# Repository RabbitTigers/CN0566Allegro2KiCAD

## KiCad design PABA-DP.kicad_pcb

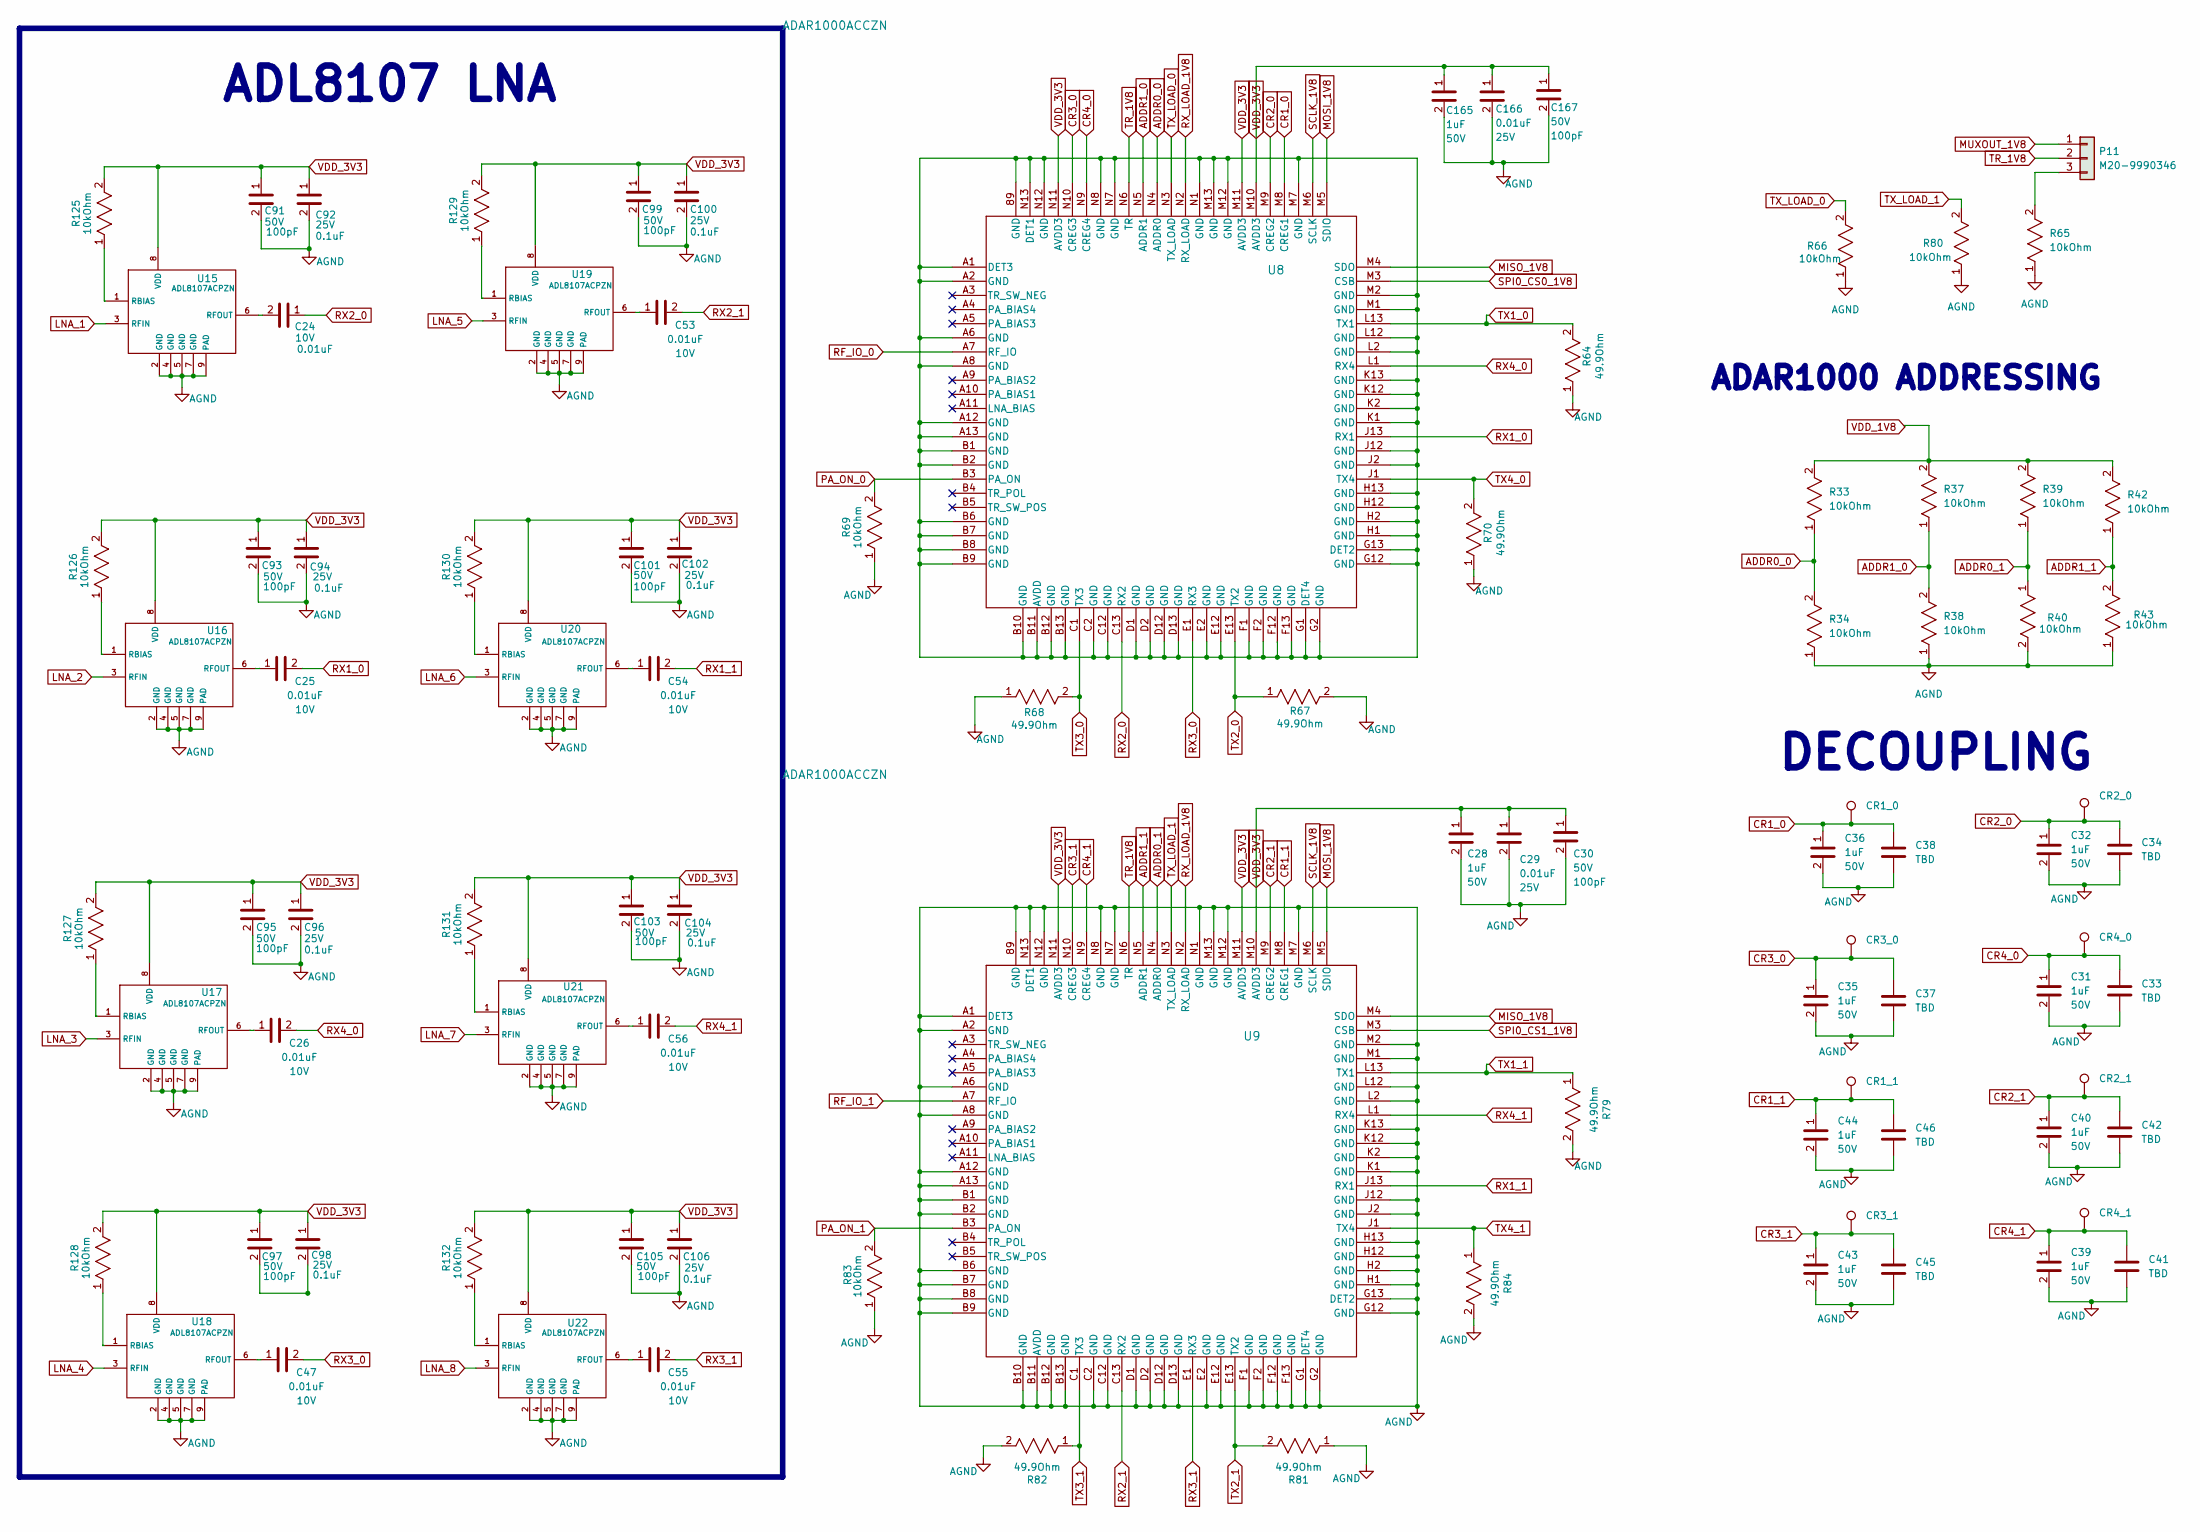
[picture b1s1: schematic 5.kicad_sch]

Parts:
C24, C25, C26, C47, C53, C54, C55, C56: GRM033R71A103KA01D; C_0201_0603Metric
C28, C31, C32, C35, C36, C39, C40, C43, C44, C165: CL10A105KB8NNNC; C_0603_1608Metric
C29, C166: CL10B103KA8NNNC; C_0603_1608Metric
C30, C91, C93, C95, C97, C99, C101, C103, C105, C167: CC0603KRX7R9BB101; C_0603_1608Metric
C33, C34, C37, C38, C41, C42, C45, C46: TBD; C_0402_1005Metric
C92, C94, C96, C98, C100, C102, C104, C106: CL10B104KA8NNNC; C_0603_1608Metric
CR1_0, CR1_1, CR2_0, CR2_1, CR3_0, CR3_1, CR4_0, CR4_1: TestPoint; Testpoint
P11: M20-9990346; PinHeader_1x03_P2.54mm_Vertical
R33, R34, R37, R38, R39, R40, R42, R43, R65, R66, R69, R80, R83, R125, R126, R127, R128, R129, R130, R131, R132: ERJ-3EKF1002V; R_0603_1608Metric
R64, R67, R68, R70, R79, R81, R82, R84: ERJ-1GNF49R9C; R_0201_0603Metric
U8, U9: ADAR1000ACCZN
U15, U16, U17, U18, U19, U20, U21, U22: ADL8107ACPZN; ADL8107ACPZN-R7

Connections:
ADDR0_0: U8.N4 (ADDR0)
ADDR0_1: R39.1, R40.1, U9.N4 (ADDR0)
ADDR1_0: R37.1, R38.2, U8.N5 (ADDR1)
ADDR1_1: R42.1, R43.2, U9.N5 (ADDR1)
AGND: C28.2, C29.2, C30.2, C31.2, C32.2, C33.2, C34.2, C35.2, C36.2, C37.2, C38.2, C39.2, C40.2, C41.2, C42.2, C43.2, C44.2, C45.2, C46.2, C91.2, C92.2, C93.2, C94.2, C95.2, C96.2, C99.2, C100.2, C101.2, C102.2, C103.2, C104.2, C105.2, C106.2, C165.2, C166.2, C167.2, R34.1, R38.1, R40.2, R43.1, R64.1, R65.1, R66.1, R67.2, R68.1, R69.1, R70.1, R79.2, R80.1, R81.1, R82.2, R83.1, R84.2, U9.89 (GND), U9.A1 (DET3), U9.A2 (GND), U9.A6 (GND), U9.A8 (GND), U9.A12 (GND), U9.A13 (GND), U9.B1 (GND), U9.B2 (GND), U9.B6 (GND), U9.B7 (GND), U9.B8 (GND), U9.B9 (GND), U9.B10 (GND), U9.B11 (AVDD), U9.B12 (GND), U9.B13 (GND), U9.C2 (GND), U9.C12 (GND), U9.D1 (GND), U9.D2 (GND), U9.D12 (GND), U9.D13 (GND), U9.E2 (GND), U9.E12 (GND), U9.F1 (GND), U9.F2 (GND), U9.F12 (GND), U9.F13 (GND), U9.G1 (DET4), U9.G2 (GND), U9.G12 (GND), U9.G13 (DET2), U9.H1 (GND), U9.H2 (GND), U9.H12 (GND), U9.H13 (GND), U9.J2 (GND), U9.J12 (GND), U9.K1 (GND), U9.K2 (GND), U9.K12 (GND), U9.K13 (GND), U9.L2 (GND), U9.L12 (GND), U9.M1 (GND), U9.M2 (GND), U9.M7 (GND), U9.M12 (GND), U9.M13 (GND), U9.N1 (GND), U9.N7 (GND), U9.N8 (GND), U9.N12 (GND), U9.N13 (DET1), U15.2 (GND), U15.4 (GND), U15.5 (GND), U15.7 (GND), U15.9 (PAD), U16.2 (GND), U16.4 (GND), U16.5 (GND), U16.7 (GND), U16.9 (PAD), U17.2 (GND), U17.4 (GND), U17.5 (GND), U17.7 (GND), U17.9 (PAD), U18.2 (GND), U18.4 (GND), U18.5 (GND), U18.7 (GND), U18.9 (PAD), U19.2 (GND), U19.4 (GND), U19.5 (GND), U19.7 (GND), U19.9 (PAD), U20.2 (GND), U20.4 (GND), U20.5 (GND), U20.7 (GND), U20.9 (PAD), U21.2 (GND), U21.4 (GND), U21.5 (GND), U21.7 (GND), U21.9 (PAD), U22.2 (GND), U22.4 (GND), U22.5 (GND), U22.7 (GND), U22.9 (PAD); also elsewhere on the board
CR1_0: C36.1, C38.1, CR1_0.1, U8.M8 (CREG1)
CR1_1: C44.1, C46.1, CR1_1.1, U9.M8 (CREG1)
CR2_0: C32.1, C34.1, CR2_0.1, U8.M9 (CREG2)
CR2_1: C40.1, C42.1, CR2_1.1, U9.M9 (CREG2)
CR3_0: C35.1, C37.1, CR3_0.1, U8.N10 (CREG3)
CR3_1: C43.1, C45.1, CR3_1.1, U9.N10 (CREG3)
CR4_0: C31.1, C33.1, CR4_0.1, U8.N9 (CREG4)
CR4_1: C39.1, C41.1, CR4_1.1, U9.N9 (CREG4)
LNA_1: U15.3 (RFIN); also elsewhere on the board
LNA_2: U16.3 (RFIN); also elsewhere on the board
LNA_3: U17.3 (RFIN); also elsewhere on the board
LNA_4: U18.3 (RFIN); also elsewhere on the board
LNA_5: U19.3 (RFIN); also elsewhere on the board
LNA_6: U20.3 (RFIN); also elsewhere on the board
LNA_7: U21.3 (RFIN); also elsewhere on the board
LNA_8: U22.3 (RFIN); also elsewhere on the board
MISO_1V8: U8.M4 (SDO), U9.M4 (SDO); also elsewhere on the board
MOSI_1V8: U8.M5 (SDIO), U9.M5 (SDIO); also elsewhere on the board
MUXOUT_1V8: P11.1; also elsewhere on the board
unnamed: C97.2, C98.2
unnamed: P11.3, R65.2
unnamed: R33.1, R34.2
unnamed: U8.89 (GND), U8.A1 (DET3), U8.A2 (GND), U8.A6 (GND), U8.A8 (GND), U8.A12 (GND), U8.A13 (GND), U8.B1 (GND), U8.B2 (GND), U8.B6 (GND), U8.B7 (GND), U8.B8 (GND), U8.B9 (GND), U8.B10 (GND), U8.B11 (AVDD), U8.B12 (GND), U8.B13 (GND), U8.C2 (GND), U8.C12 (GND), U8.D1 (GND), U8.D2 (GND), U8.D12 (GND), U8.D13 (GND), U8.E2 (GND), U8.E12 (GND), U8.F1 (GND), U8.F2 (GND), U8.F12 (GND), U8.F13 (GND), U8.G1 (DET4), U8.G2 (GND), U8.G12 (GND), U8.G13 (DET2), U8.H1 (GND), U8.H2 (GND), U8.H12 (GND), U8.H13 (GND), U8.J2 (GND), U8.J12 (GND), U8.K1 (GND), U8.K2 (GND), U8.K12 (GND), U8.K13 (GND), U8.L2 (GND), U8.L12 (GND), U8.M1 (GND), U8.M2 (GND), U8.M7 (GND), U8.M12 (GND), U8.M13 (GND), U8.N1 (GND), U8.N7 (GND), U8.N8 (GND), U8.N12 (GND), U8.N13 (DET1)
unnamed: R125.1, U15.1 (RBIAS)
unnamed: C24.2, U15.6 (RFOUT)
unnamed: R126.1, U16.1 (RBIAS)
unnamed: C25.1, U16.6 (RFOUT)
unnamed: R127.1, U17.1 (RBIAS)
unnamed: C26.1, U17.6 (RFOUT)
unnamed: R128.1, U18.1 (RBIAS)
unnamed: C47.1, U18.6 (RFOUT)
unnamed: R129.1, U19.1 (RBIAS)
unnamed: C53.1, U19.6 (RFOUT)
unnamed: R130.1, U20.1 (RBIAS)
unnamed: C54.1, U20.6 (RFOUT)
unnamed: R131.1, U21.1 (RBIAS)
unnamed: C56.1, U21.6 (RFOUT)
unnamed: R132.1, U22.1 (RBIAS)
unnamed: C55.1, U22.6 (RFOUT)
PA_ON_0: R69.2, U8.B3 (PA_ON)
PA_ON_1: R83.2, U9.B3 (PA_ON)
RF_IO_0: U8.A7 (RF_IO); also elsewhere on the board
RF_IO_1: U9.A7 (RF_IO); also elsewhere on the board
RX1_0: C25.2, U8.J13 (RX1)
RX1_1: C54.2, U9.J13 (RX1)
RX2_0: C24.1, U8.C13 (RX2)
RX2_1: C53.2, U9.C13 (RX2)
RX3_0: C47.2, U8.E1 (RX3)
RX3_1: C55.2, U9.E1 (RX3)
RX4_0: C26.2, U8.L1 (RX4)
RX4_1: C56.2, U9.L1 (RX4)
RX_LOAD_1V8: U8.N2 (RX_LOAD), U9.N2 (RX_LOAD); also elsewhere on the board
SCLK_1V8: U8.M6 (SCLK), U9.M6 (SCLK); also elsewhere on the board
SPI0_CS0_1V8: U8.M3 (CSB); also elsewhere on the board
SPI0_CS1_1V8: U9.M3 (CSB); also elsewhere on the board
TR_1V8: P11.2, U8.N6 (TR), U9.N6 (TR); also elsewhere on the board
TX1_0: R64.2, U8.L13 (TX1)
TX1_1: R79.1, U9.L13 (TX1)
TX2_0: R67.1, U8.E13 (TX2)
TX2_1: R81.2, U9.E13 (TX2)
TX3_0: R68.2, U8.C1 (TX3)
TX3_1: R82.1, U9.C1 (TX3)
TX4_0: R70.2, U8.J1 (TX4)
TX4_1: R84.1, U9.J1 (TX4)
TX_LOAD_0: R66.2, U8.N3 (TX_LOAD)
TX_LOAD_1: R80.2, U9.N3 (TX_LOAD)
VDD_1V8: R33.2, R37.2, R39.2, R42.2; also elsewhere on the board
VDD_3V3: C28.1, C29.1, C30.1, C91.1, C92.1, C93.1, C94.1, C95.1, C96.1, C97.1, C98.1, C99.1, C100.1, C101.1, C102.1, C103.1, C104.1, C105.1, C106.1, C165.1, C166.1, C167.1, R125.2, R126.2, R127.2, R128.2, R129.2, R130.2, R131.2, R132.2, U8.M10 (AVDD3), U8.M11 (AVDD3), U8.N11 (AVDD3), U9.M10 (AVDD3), U9.M11 (AVDD3), U9.N11 (AVDD3), U15.8 (VDD), U16.8 (VDD), U17.8 (VDD), U18.8 (VDD), U19.8 (VDD), U20.8 (VDD), U21.8 (VDD), U22.8 (VDD); also elsewhere on the board

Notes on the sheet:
ADL8107 LNA
ADAR1000 ADDRESSING
DECOUPLING

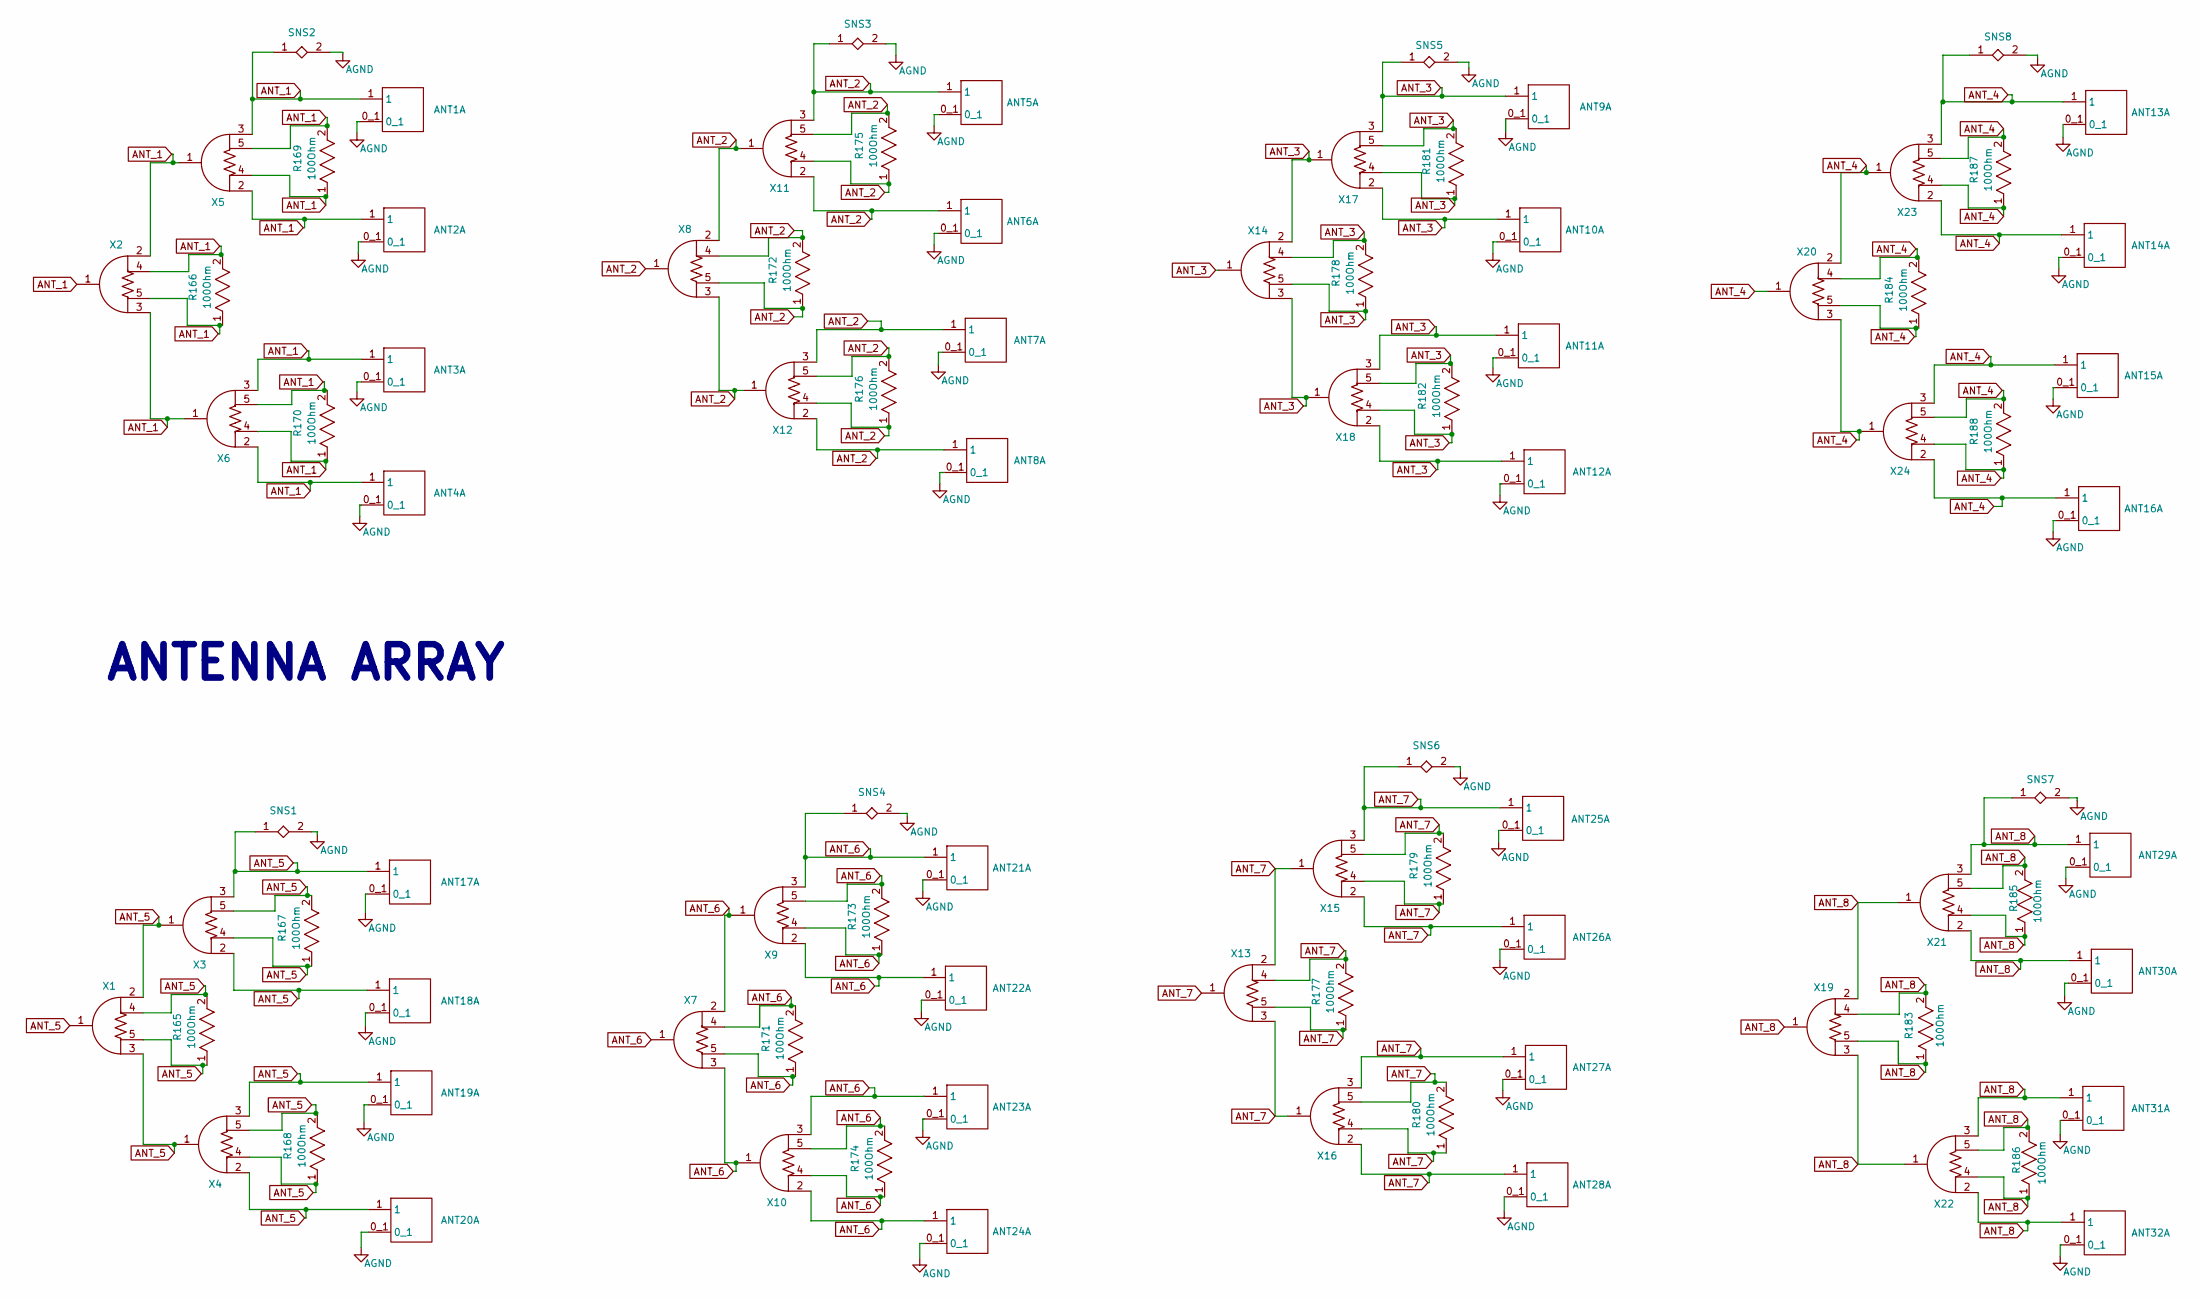
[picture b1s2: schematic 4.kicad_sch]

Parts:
ANT1, ANT2, ANT3, ANT4, ANT5, ANT6, ANT7, ANT8, ANT9, ANT10, ANT11, ANT12, ANT13, ANT14, ANT15, ANT16, ANT17, ANT18, ANT19, ANT20, ANT21, ANT22, ANT23, ANT24, ANT25, ANT26, ANT27, ANT28, ANT29, ANT30, ANT31, ANT32: Patch_Ant; Patch Antenna
R165, R166, R167, R168, R169, R170, R171, R172, R173, R174, R175, R176, R177, R178, R179, R180, R181, R182, R183, R184, R185, R186, R187, R188: ERJ-2RKF1000X; R_0402_1005Metric
SNS1, SNS2, SNS3, SNS4, SNS5, SNS6, SNS7, SNS8: NCSNS20MILL; SNS50Mill
X1, X2, X3, X4, X5, X6, X7, X8, X9, X10, X11, X12, X13, X14, X15, X16, X17, X18, X19, X20, X21, X22, X23, X24: 5P_Wilkinson_Divider; 5Pos Wilkinson divider

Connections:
AGND: ANT1.0_1, ANT2.0_1, ANT3.0_1, ANT4.0_1, ANT5.0_1, ANT6.0_1, ANT7.0_1, ANT8.0_1, ANT9.0_1, ANT10.0_1, ANT11.0_1, ANT12.0_1, ANT13.0_1, ANT14.0_1, ANT15.0_1, ANT16.0_1, ANT17.0_1, ANT18.0_1, ANT19.0_1, ANT20.0_1, ANT21.0_1, ANT22.0_1, ANT23.0_1, ANT24.0_1, ANT25.0_1, ANT26.0_1, ANT27.0_1, ANT28.0_1, ANT29.0_1, ANT30.0_1, ANT31.0_1, ANT32.0_1, SNS1.2, SNS2.2, SNS3.2, SNS4.2, SNS5.2, SNS6.2, SNS7.2, SNS8.2; also elsewhere on the board
ANT_1: ANT1.1, ANT2.1, ANT3.1, ANT4.1, R166.1, R166.2, R169.1, R169.2, R170.1, R170.2, SNS2.1, X2.1, X2.2, X2.3, X2.4, X2.5, X5.1, X5.2, X5.3, X5.4, X5.5, X6.1, X6.2, X6.3, X6.4, X6.5; also elsewhere on the board
ANT_2: ANT5.1, ANT6.1, ANT7.1, ANT8.1, R172.1, R172.2, R175.1, R175.2, R176.1, R176.2, SNS3.1, X8.1, X8.2, X8.3, X8.4, X8.5, X11.1, X11.2, X11.3, X11.4, X11.5, X12.1, X12.2, X12.3, X12.4, X12.5; also elsewhere on the board
ANT_3: ANT9.1, ANT10.1, ANT11.1, ANT12.1, R178.1, R178.2, R181.1, R181.2, R182.1, R182.2, SNS5.1, X14.1, X14.2, X14.3, X14.4, X14.5, X17.1, X17.2, X17.3, X17.4, X17.5, X18.1, X18.2, X18.3, X18.4, X18.5; also elsewhere on the board
ANT_4: ANT13.1, ANT14.1, ANT15.1, ANT16.1, R184.1, R184.2, R187.1, R187.2, R188.1, R188.2, SNS8.1, X20.1, X20.2, X20.3, X20.4, X20.5, X23.1, X23.2, X23.3, X23.4, X23.5, X24.1, X24.2, X24.3, X24.4, X24.5; also elsewhere on the board
ANT_5: ANT17.1, ANT18.1, ANT19.1, ANT20.1, R165.1, R165.2, R167.1, R167.2, R168.1, R168.2, SNS1.1, X1.1, X1.2, X1.3, X1.4, X1.5, X3.1, X3.2, X3.3, X3.4, X3.5, X4.1, X4.2, X4.3, X4.4, X4.5; also elsewhere on the board
ANT_6: ANT21.1, ANT22.1, ANT23.1, ANT24.1, R171.1, R171.2, R173.1, R173.2, R174.1, R174.2, SNS4.1, X7.1, X7.2, X7.3, X7.4, X7.5, X9.1, X9.2, X9.3, X9.4, X9.5, X10.1, X10.2, X10.3, X10.4, X10.5; also elsewhere on the board
ANT_7: ANT25.1, ANT26.1, ANT27.1, ANT28.1, R177.1, R177.2, R179.1, R179.2, R180.1, R180.2, SNS6.1, X13.1, X13.2, X13.3, X13.4, X13.5, X15.1, X15.2, X15.3, X15.4, X15.5, X16.1, X16.2, X16.3, X16.4, X16.5; also elsewhere on the board
ANT_8: ANT29.1, ANT30.1, ANT31.1, ANT32.1, R183.1, R183.2, R185.1, R185.2, R186.1, R186.2, SNS7.1, X19.1, X19.2, X19.3, X19.4, X19.5, X21.1, X21.2, X21.3, X21.4, X21.5, X22.1, X22.2, X22.3, X22.4, X22.5; also elsewhere on the board

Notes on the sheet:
ANTENNA ARRAY

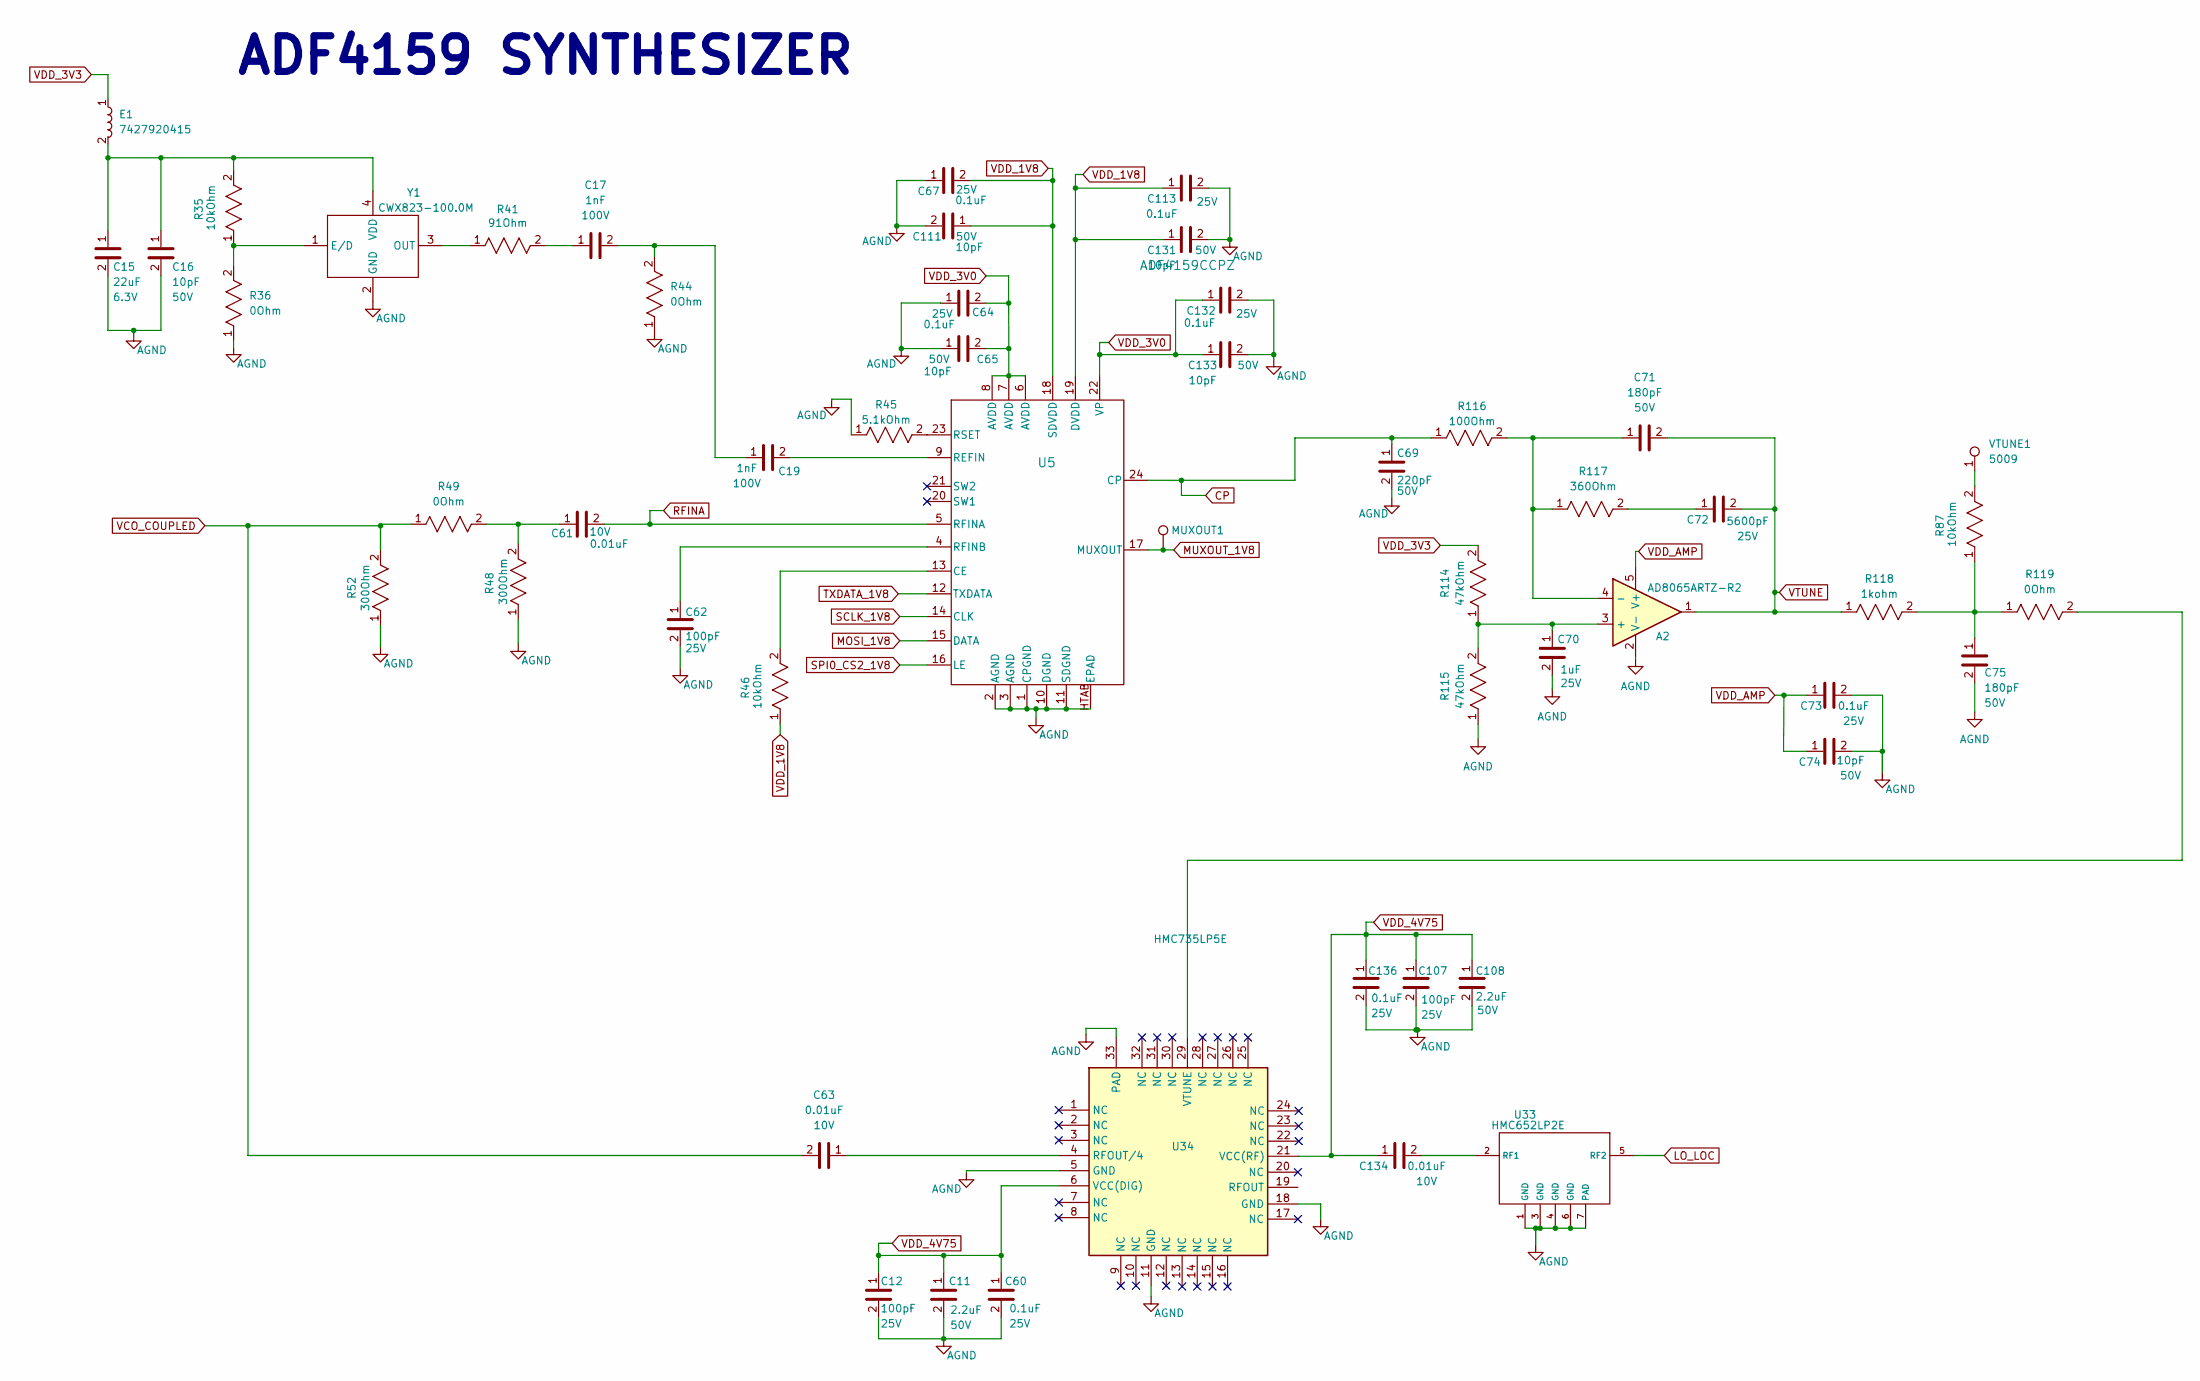
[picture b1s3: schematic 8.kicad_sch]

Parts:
A2: AD8065ARTZ-R2; SOT-23-5
C11, C108: GRM188R61H225KE11J; C_0603_1608Metric
C12, C62, C107: GRM033R71E101KA01D; C_0201_0603Metric
C15: GRM21BR60J226ME39L; C_0805_2012Metric
C16, C65, C74, C111, C131, C133: CC0402JRNPO9BN100; C_0402_1005Metric
C17, C19: 06031C102KAT2A; C_0603_1608Metric
C60, C64, C67, C73, C113, C132, C136: GRM155R71E104KE14D; C_0402_1005Metric
C61, C63, C134: GRM033R71A103KA01D; C_0201_0603Metric
C69: GRM0335C1H221JA01D; C_0201_0603Metric
C70: C1005X5R1E105K050BC; C_0402_1005Metric
C71, C75: CL05C181JB5NNNC; C_0402_1005Metric
C72: C0603C562J3GACTU; C_0603_1608Metric
E1: 7427920415; L_0805_2012Metric_Pad1.05x1.20mm_HandSolder
MUXOUT1: TestPoint; Testpoint
R35, R46, R87: ERJ-1GNF1002C; R_0201_0603Metric
R36, R44, R49, R119: ERJ-2GE0R00X; R_0402_1005Metric
R41: RC0603FR-0791RL; R_0603_1608Metric
R45: ERJ-1GNF5101C; R_0201_0603Metric
R48, R52: ERJ-1GNF3000C; R_0201_0603Metric
R114, R115: ERJ-1GNF4702C; R_0201_0603Metric
R116: ERJ-2RKF1000X; R_0402_1005Metric
R117: ERJ-2GEJ361X; R_0402_1005Metric
R118: ERJ-1GNF1001C; R_0201_0603Metric
U5: ADF4159CCPZ
U33: HMC652LP2E; HMC652LP2E TDFN 2x2
U34: HMC735LP5E; QFN-32-1EP_5x5mm_P0.5mm_EP3.7x3.7mm
VTUNE1: 5009; KEYSTONE_5009
Y1: CWX823-100.0M

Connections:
AGND: A2.2 (V-), C11.2, C12.2, C15.2, C16.2, C60.2, C62.2, C64.1, C65.1, C67.1, C69.2, C70.2, C73.2, C74.2, C75.2, C107.2, C108.2, C111.2, C113.2, C131.2, C132.2, C133.2, C136.2, R36.1, R44.1, R45.1, R48.1, R52.1, R115.1, U5.1 (CPGND), U5.2 (AGND), U5.3 (AGND), U5.10 (DGND), U5.11 (SDGND), U5.HTAB (EPAD), U33.1 (GND), U33.3 (GND), U33.4 (GND), U33.6 (GND), U33.7 (PAD), U34.5 (GND), U34.11 (GND), U34.18 (GND), U34.33 (PAD), Y1.2 (GND); also elsewhere on the board
CP: C69.1, R116.1, U5.24 (CP)
LO_LOC: U33.5 (RF2); also elsewhere on the board
MOSI_1V8: U5.15 (DATA); also elsewhere on the board
MUXOUT_1V8: MUXOUT1.1, U5.17 (MUXOUT); also elsewhere on the board
unnamed: A2.3 (+), C70.1, R114.1, R115.2
unnamed: A2.4 (-), C71.1, R116.2, R117.1
unnamed: C17.1, R41.2
unnamed: C17.2, C19.1, R44.2
unnamed: C61.1, R48.2, R49.2
unnamed: C72.1, R117.2
unnamed: C75.1, R87.1, R118.2, R119.1
unnamed: R87.2, VTUNE1.1
unnamed: R46.2, U5.13 (CE)
unnamed: C19.2, U5.9 (REFIN)
unnamed: C62.1, U5.4 (RFINB)
unnamed: R45.2, U5.23 (RSET)
unnamed: C134.2, U33.2 (RF1)
unnamed: C63.1, U34.4 (RFOUT/4)
unnamed: R119.2, U34.29 (VTUNE)
unnamed: R35.1, R36.2, Y1.1 (E/D)
unnamed: R41.1, Y1.3 (OUT)
unnamed: C15.1, C16.1, E1.2, R35.2, Y1.4 (VDD)
RFINA: C61.2, U5.5 (RFINA)
SCLK_1V8: U5.14 (CLK); also elsewhere on the board
SPI0_CS2_1V8: U5.16 (LE); also elsewhere on the board
TXDATA_1V8: U5.12 (TXDATA); also elsewhere on the board
VCO_COUPLED: C63.2, R49.1, R52.2
VDD_1V8: C67.2, C111.1, C113.1, C131.1, R46.1, U5.18 (SDVDD), U5.19 (DVDD); also elsewhere on the board
VDD_3V0: C64.2, C65.2, C132.1, C133.1, U5.6 (AVDD), U5.7 (AVDD), U5.8 (AVDD), U5.22 (VP); also elsewhere on the board
VDD_3V3: E1.1, R114.2; also elsewhere on the board
VDD_4V75: C11.1, C12.1, C60.1, C107.1, C108.1, C134.1, C136.1, U34.6 (VCC(DIG)), U34.21 (VCC(RF)); also elsewhere on the board
VDD_AMP: A2.5 (V+), C73.1, C74.1; also elsewhere on the board
VTUNE: A2.1, C71.2, C72.2, R118.1; also elsewhere on the board

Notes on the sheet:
ADF4159 SYNTHESIZER

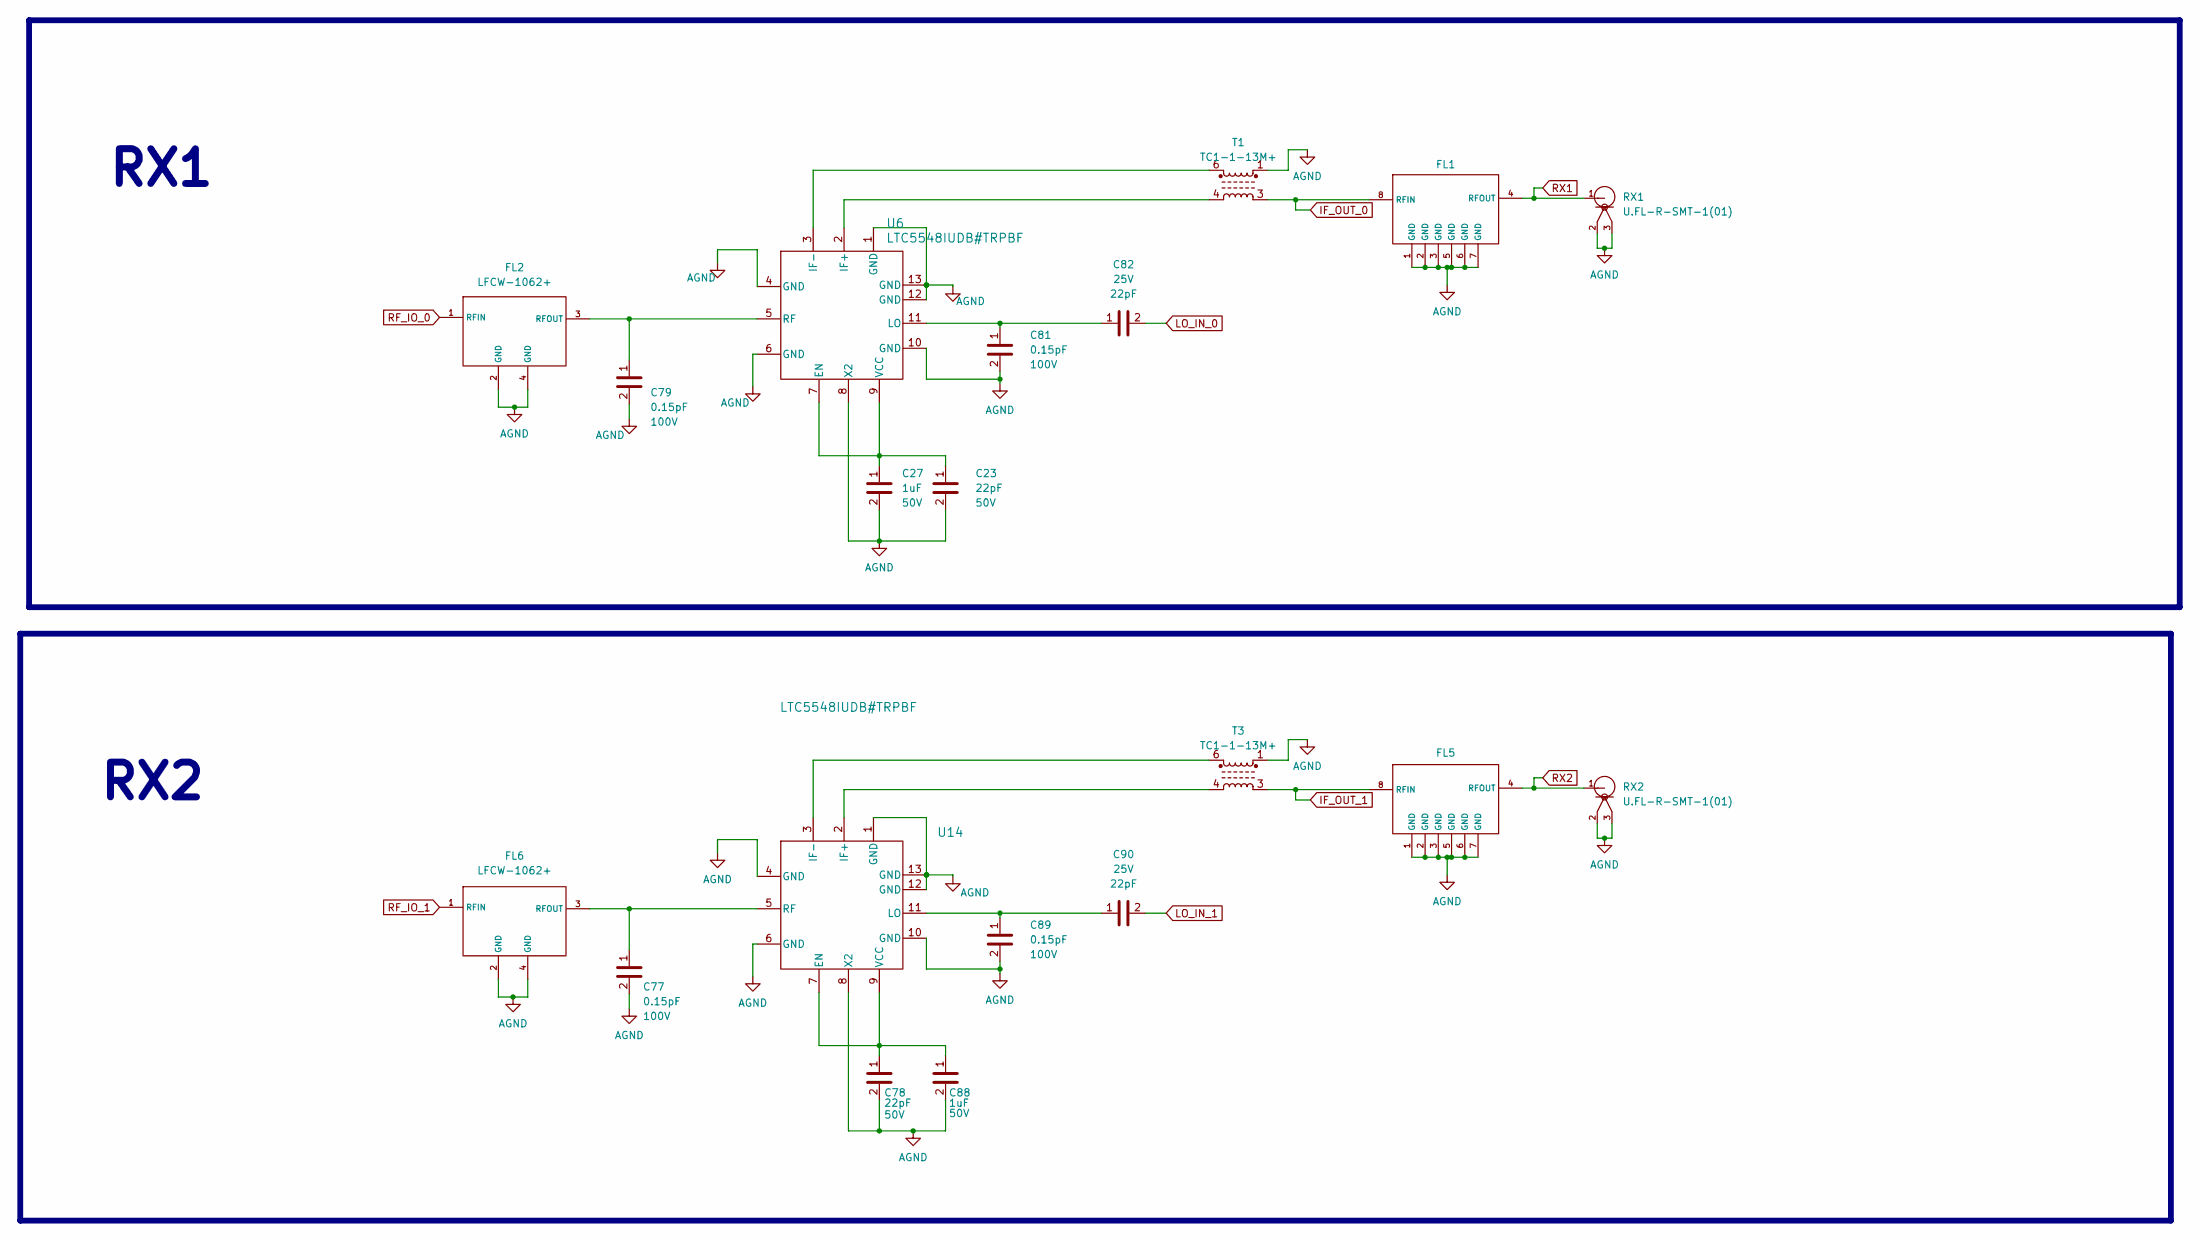
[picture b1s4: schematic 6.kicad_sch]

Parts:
C23, C78: 06035C220JAT2A; C_0603_1608Metric
C27, C88: CL10A105KB8NNNC; C_0603_1608Metric
C77, C79, C81, C89: 02011JR15ZBSTR; C_0201_0603Metric
C82, C90: GRM0335C1E220JA01D; C_0201_0603Metric
FL1, FL5: LFCG-2500+; LFCG2500
FL2, FL6: LFCW-1062+
RX1, RX2: U.FL-R-SMT-1(01); COAX2_U.FL-R-SMT-101_HIR
T1, T3: TC1-1-13M+
U6, U14: LTC5548IUDB#TRPBF

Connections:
AGND: C23.2, C27.2, C77.2, C78.2, C79.2, C81.2, C88.2, C89.2, FL1.1 (GND), FL1.2 (GND), FL1.3 (GND), FL1.5 (GND), FL1.6 (GND), FL1.7 (GND), FL2.2 (GND), FL2.4 (GND), FL5.1 (GND), FL5.2 (GND), FL5.3 (GND), FL5.5 (GND), FL5.6 (GND), FL5.7 (GND), FL6.2 (GND), FL6.4 (GND), RX1.2, RX1.3, RX2.2, RX2.3, T1.1, T3.1, U6.1 (GND), U6.4 (GND), U6.6 (GND), U6.8 (X2), U6.10 (GND), U6.12 (GND), U6.13 (GND), U14.1 (GND), U14.4 (GND), U14.6 (GND), U14.8 (X2), U14.10 (GND), U14.12 (GND), U14.13 (GND); also elsewhere on the board
IF_OUT_0: FL1.8 (RFIN), T1.3
IF_OUT_1: FL5.8 (RFIN), T3.3
LO_IN_0: C82.2; also elsewhere on the board
LO_IN_1: C90.2; also elsewhere on the board
unnamed: C79.1, FL2.3 (RFOUT), U6.5 (RF)
unnamed: C77.1, FL6.3 (RFOUT), U14.5 (RF)
unnamed: C23.1, C27.1, U6.7 (EN), U6.9 (VCC)
unnamed: T1.4, U6.2 (IF+)
unnamed: T1.6, U6.3 (IF-)
unnamed: C81.1, C82.1, U6.11 (LO)
unnamed: C78.1, C88.1, U14.7 (EN), U14.9 (VCC)
unnamed: T3.4, U14.2 (IF+)
unnamed: T3.6, U14.3 (IF-)
unnamed: C89.1, C90.1, U14.11 (LO)
RF_IO_0: FL2.1 (RFIN); also elsewhere on the board
RF_IO_1: FL6.1 (RFIN); also elsewhere on the board
RX1: FL1.4 (RFOUT), RX1.1
RX2: FL5.4 (RFOUT), RX2.1

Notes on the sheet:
RX2
RX1
